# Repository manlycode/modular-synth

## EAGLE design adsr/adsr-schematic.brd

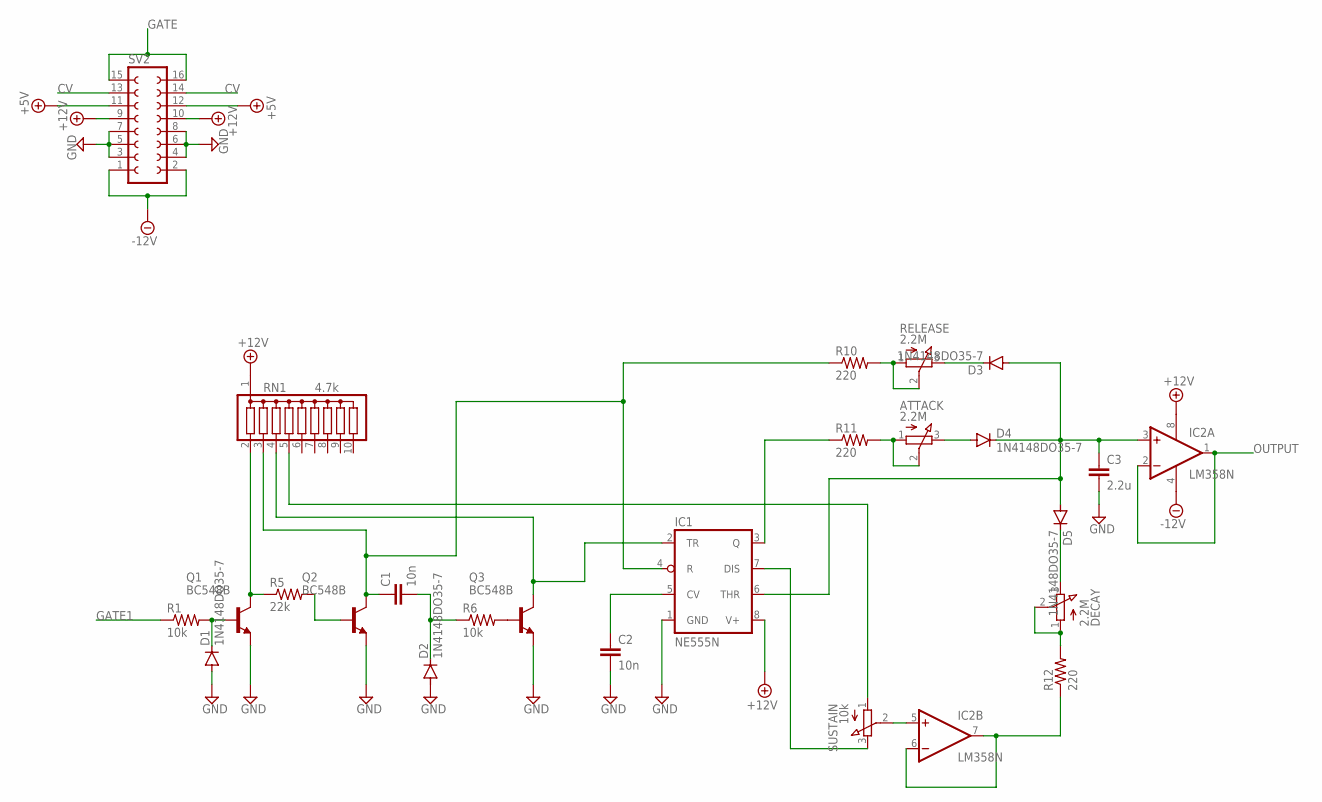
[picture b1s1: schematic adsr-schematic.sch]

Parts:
ATTACK: 2.2M; 3RP/1610N
C1, C2: 10n; C2.5-4
C3: 2.2u; C2.5-4
D1, D2, D3, D4, D5: 1N4148DO35-7; DO35-7
DECAY: 2.2M; 3RP/1610N
IC1: NE555N; DIL08
IC2: LM358N; DIL08
Q1, Q2, Q3: BC548B; TO92-EBC
R1, R6: 10k; 0204/5
R5: 22k; 0204/5
R10, R11, R12: 220; 0204/5
RELEASE: 2.2M; 3RP/1610N
RN1: 4.7k; SIL10
SUSTAIN: 10k; 3RP/1610N
SV2: FE08-2W

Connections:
+5V: SV2.11, SV2.12
+12V: IC1.8 (V+), IC2.8 (V+), RN1.1, SV2.9, SV2.10
-12V: IC2.4 (V-), SV2.1, SV2.2
CV: SV2.13, SV2.14
GATE: SV2.15, SV2.16
GATE1: R1.1
GND: C2.2, C3.2, D1.A, D2.A, IC1.1 (GND), Q1.E, Q2.E, Q3.E, SV2.3, SV2.4, SV2.5, SV2.6, SV2.7, SV2.8
unnamed: D1.C, Q1.B, R1.2
unnamed: Q1.C, R5.1, RN1.2
unnamed: C1.1, IC1.4 (R), Q2.C, R10.1, RN1.3
unnamed: IC1.2 (TR), Q3.C, RN1.4
unnamed: Q2.B, R5.2
unnamed: Q3.B, R6.2
unnamed: C1.2, D2.C, R6.1
unnamed: R10.2, RELEASE.1 (A), RELEASE.2 (S)
unnamed: ATTACK.1 (A), ATTACK.2 (S), R11.2
unnamed: DECAY.1 (A), DECAY.2 (S), R12.2
unnamed: ATTACK.3 (E), D4.A
unnamed: C3.1, D3.A, D4.C, D5.A, IC1.6 (THR), IC2.3 (+IN)
unnamed: D5.C, DECAY.3 (E)
unnamed: IC1.3 (Q), R11.1
unnamed: C2.1, IC1.5 (CV)
unnamed: IC2.5 (+IN), SUSTAIN.2 (S)
unnamed: RN1.5, SUSTAIN.1 (A)
unnamed: IC2.6 (-IN), IC2.7 (OUT), R12.1
unnamed: D3.C, RELEASE.3 (E)
unnamed: IC1.7 (DIS), SUSTAIN.3 (E)
OUTPUT: IC2.1 (OUT), IC2.2 (-IN)

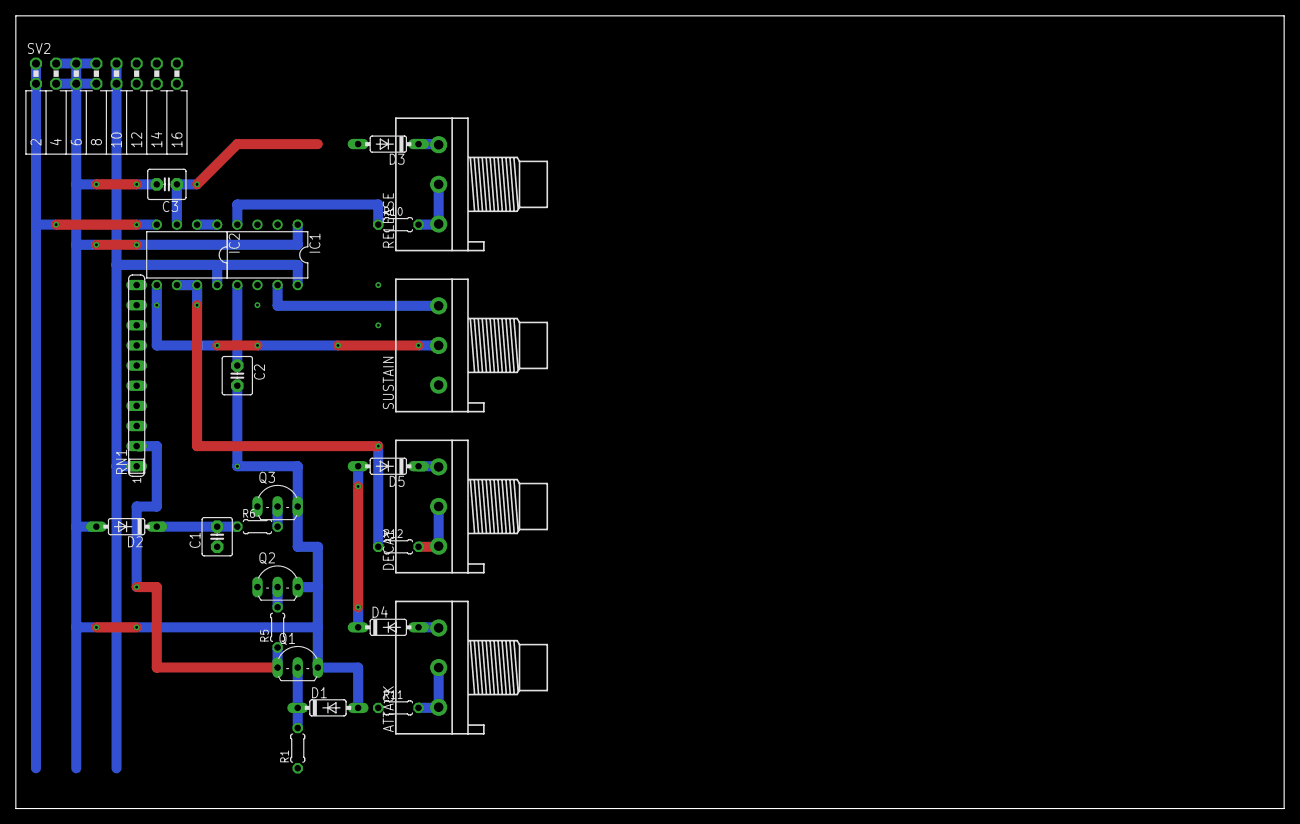
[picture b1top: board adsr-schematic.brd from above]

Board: 2 copper layers, 160.0 x 100.0 mm, 25 parts (0 on the bottom side), 27 nets.

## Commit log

2020-01-23 Initial commit.
2020-01-23 Configure tempo for sequencer.
2020-01-23 Add counter ouput.
2020-01-29 Use 8 pins to display beat.
2020-02-10 Add code for sequencer.
2020-03-14 add android-vco
2020-03-14 Cycle through waveforms for modular synth.
2020-03-15 Add button press.
2020-03-15 Add cursor selection for button press.
2020-03-15 Playing with pwm.
2020-03-18 Spiking into mozzi and OLED
2020-03-18 Clean up.
2020-03-20 Add Android VCO project.
2020-03-20 Add encoder test.
2020-03-20 Add Handy POST.
2020-03-20 Add a test for buttons.
2020-03-21 Test control voltage input.
2020-03-21 Switch waves.
2020-03-21 Try (and fail) to calculate frequency.
2020-03-21 Update frequency based on input.
2020-03-22 Tweaks.
2020-04-10 add adsr'
2020-04-11 update midi-to-cv schematic.
2020-04-14 save sequencer and adsr.
2020-04-16 Update schematic
2020-04-16 add arduino-vco-dac
2020-04-17 Working example with DAC
2020-05-18 Save point for vco.
2020-05-23 Pare down Arduino DAC oscillator.
2020-05-26 Add models for multi-vca
2021-06-16 added dual vco.
2021-06-20 Start design of ADSR.
2021-06-20 Add adsr
2021-06-20 Basic power supply
2021-09-12 Add power supply files.
